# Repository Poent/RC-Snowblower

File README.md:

# RC Snowblower Project

====
LATEST UPDATES (10-26-2025):

Working on designing the impeller and auger portion of the snowblower. Switched from using a worm gear assembly to a custom ring and pinion setup using a spiral bevel gear. Motor is a 190KV motor being driven at 38v nominal. Motor at full power (which we'll never do) will spin at about 7,200 RPM. the motor goes through a 3:1 reduction to the impeller. Impeller will spin at <2400 RPM. The impeller drives the input shaft of the auger gearbox, which has a 9:1 reduction. At full power that will result in the auger at about 250rpm. All of these are design maximums. The motor will likely be RPM limited to 60% total power in the VESC, more than halving all these totals. 

Hello everyone! Welcome to my crazy project.

Before diving into the details, here’s quick background on me and why I’m building this. Feel free to skip down to the status if you want the meat.

=====

### Who I am
I’m a tech leader in the OT/MSP space with ~15 years in IT services. I own our MSP tool stack, cybersecurity program, and AI/automation initiatives. I’m CISSP-certified and studied electrical engineering, game development/design, and aviation management in college. I have a wonderful wife and two kids, and my hobbies include art, design, programming, 3D printing, woodworking, and more.

### How this project started
About two years ago my wife sent me a video of the Yarbo snowblower. It’s a tracked outdoor platform with attachments for mowing, snowblowing, hauling, etc., and it can go fully autonomous with an RTK/GNSS setup. I loved it… until I saw it was about $5,000, which I can’t justify for a <15-foot driveway.

Then she sent a smiliar (but different) 3D-printed snowblower video. Once again I was hyped to look at building it, but the "basic" kit alone was about $4,000. My dreams were dashed again—but the seed was planted.... I’ve got experience with CAD, 3D printing, and electronics, so I decided to try building my own!

That’s this project. While my BOM is under $4k... it is far more expensive than I initially anticipated and I have a far higher respect for those alternatives. 

### What to expect here
I can't honestly recommend anyone replicate this build. Better platforms exist, and I'm not an engineer! While I intend to make everything functional, resilient, and high quality... there WILL be problems. If you choose to follow along or, god forbid, try to build one of these yourself.... PLEASE understand what you're getting into. It WILL be a significant investment and there is NO garuntee of a working platform at the end of it. Please don't anticipate assistance of any kind if you choose to build this. BUT.... if you do... please tell me! I would love to see what other people do. I intend to make and keep this project fully open source, and I have no dreams of making this into a commercial product at any point in time. 

For those of you that want to just check it out and/or follow along - then sit back, and enjoy the ride!

## Status

**Completed**
- Chassis assembled with CNC aluminum frame and 3D-printed interconnects
- Power system using Headway 40152 LiFePO₄ cells and JK BMS
- V1 controller board designed, produced, soldered, and tested
- Basic ESP32 firmware with CRSF input and VESC CAN telemetry
- Initial drivetrain movement tests

**In Progress**
- Finalizing V1 firmware for the ESP32 and carrier board
- Universal mount for the snowblower attachment
- Track stress testing and refinement
- Chassis cover design and integration (sealed against snow)

**Planned**
- Blower attachment design and integration
- Public-ready docs for CAD, electronics, and firmware
- BOM refinement for cost and reliability

# LATEST IMAGES

# Progress

**Completed:**
- Chassis structure assembled with CNC aluminum frame and 3D-printed interconnects  
- Power system finalized around Headway LiFePO₄ cells and JK BMS (150A).
- Custom V1 of controller board - Designed, produced, soldered, and tested.
- Basic firmware running on ESP32 with input decoding and VESC telemetry working. 
- Initial testing of drivetrain and basic movement functions

**In Progress:**
- Finalize V1 Firmware for ESP32 and carrier board
- Design and implement universal mount for snowblower attachment. 
- Track stress testing and refinement
- Chassis cover design and integration (sealed against snow ingress) - NOT STARTED

**Future work:**
- Design blower attachment and integration.
- Preparing the project for public release (this repository) and planning documentation for CAD, electronics, and firmware.
- Refine parts list and BOM to reduce cost, complexity, and improve reliability.

## Overview
This repository will contain (wish list) the complete design and implementation files for a remote-controlled snowblower, including:

- **CAD Models**: 3D designs and mechanical components
- **Electronics**: Circuit designs, PCB layouts, and component specifications
- **Code**: Control software and firmware
- **Documentation**: Build guides, specifications, and user manuals
- **Images**: Photos, diagrams, and visual documentation
- **Build Log**: Chronological record of design iterations, testing, and modifications

## Repository Structure

```
├── CAD/           # 3D models, drawings, and mechanical designs
├── Code/          # Control software and firmware
├── Docs/          # Documentation and guides
├── Electronics/   # Circuit designs and electrical components
├── Images/        # Photos, diagrams, and visual documentation
└── Build_Log/    # Chronological record of design iterations and testing

```

## Features (Planned)
- [done] Remote control operation
- [done] Variable speed control
- [done] High-performance BLDC motors with custom gearboxes
- [ ] Weather-resistant design
- [ ] Modular component system
- [ ] Universal Mount for attachments (snowblower, plow, etc.)

### Wish List
- Autonomous navigation capabilities
- Real-time telemetry
- Produce fully open-source hardware and software
- Develop 3D printed versions of key components to reduce cost

## Hardware Requirements
*To be documented*

## Software Requirements
*To be documented*

## Getting Started
*Build instructions coming soon*

## Contributing
*Contribution guidelines to be added*

## License
*License information to be added*

## Contact
*Contact information to be added*

---
*This README will be updated as the project progresses.*

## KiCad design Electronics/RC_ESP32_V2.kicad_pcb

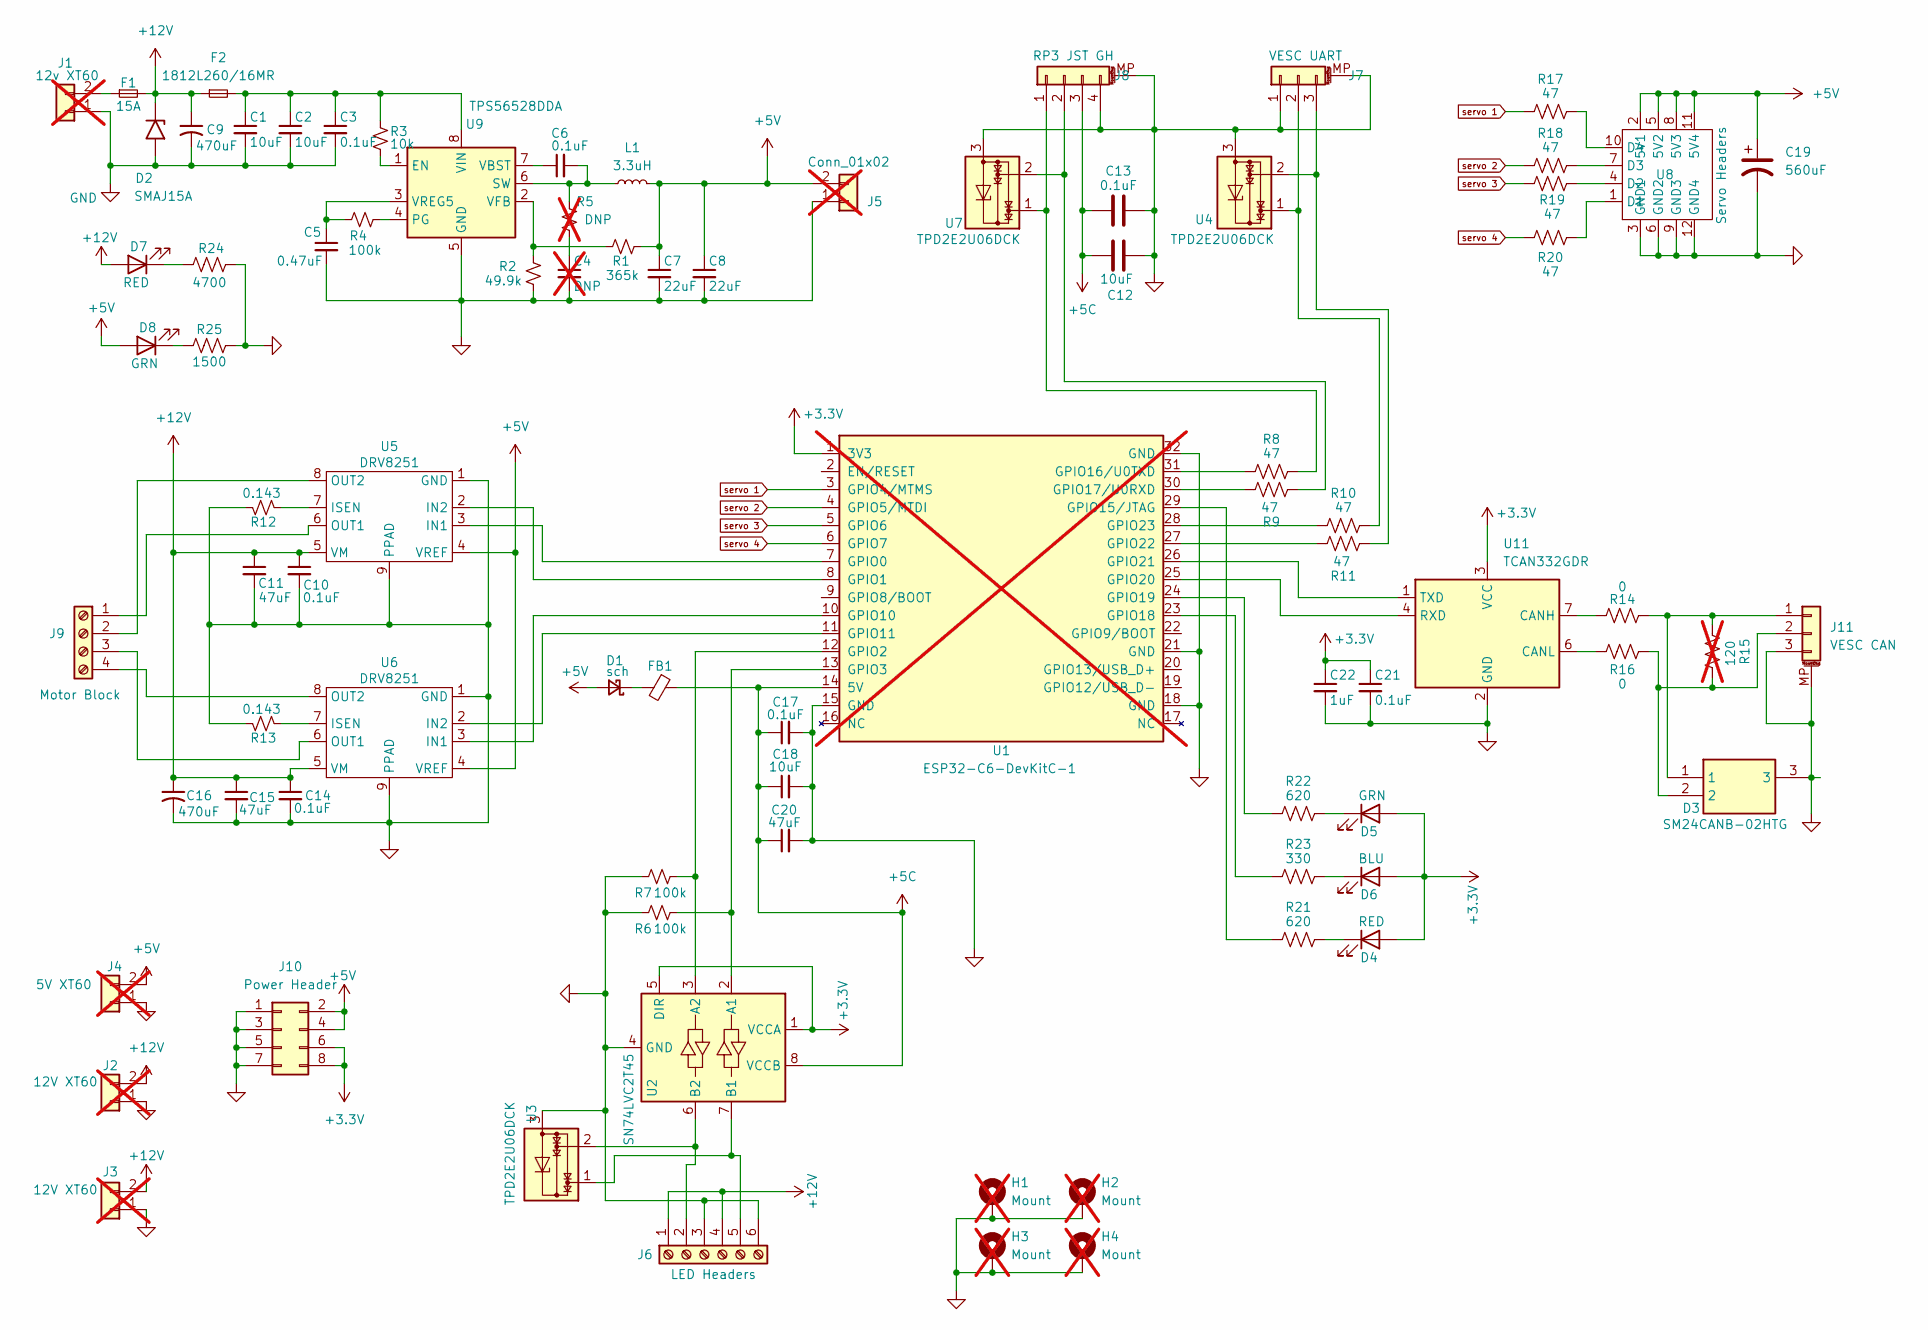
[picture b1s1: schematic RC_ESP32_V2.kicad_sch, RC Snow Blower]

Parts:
C1, C2, C12, C18: 10uF; C_0805_2012Metric_Pad1.18x1.45mm_HandSolder; MFG Part # GRM21BZ71E106KE15L
C3, C6, C10, C13, C14, C17, C21: 0.1uF; C_0805_2012Metric_Pad1.18x1.45mm_HandSolder; MFG Part # KGM21NR71E104KT
C4: DNP; C_0805_2012Metric_Pad1.18x1.45mm_HandSolder; not fitted
C5: 0.47uF; C_0805_2012Metric_Pad1.18x1.45mm_HandSolder; MFG Part # GRM188R71E474KA12D
C7, C8: 22uF; C_0805_2012Metric_Pad1.18x1.45mm_HandSolder; MFG Part # GRM21BR61C226ME44L
C9, C16: 470uF; CAP_EEHZU1E471P; MFG Part # EEH-ZU1E471P
C11, C15, C20: 47uF; C_1210_3225Metric_Pad1.33x2.70mm_HandSolder; MFG Part # TMK325ABJ476MM-P
C19: 560uF; CP_Elec_10x7.9; MFG Part # 10SVP560M
C22: 1uF; C_0805_2012Metric_Pad1.18x1.45mm_HandSolder; MFG Part # GRM21BR71A105KA01K
D1: sch; D_SOD-123; MFG Part # B5819W
D2: SMAJ15A; D_SMA; MFG Part # SMAJ15A
D3: SM24CANB-02HTG; SM24CANB02HTG; Manufacturer_Part_Number SM24CANB-02HTG; Mouser Part Number 576-SM24CANB-02HTG
D4, D7: RED; LED_1206_3216Metric_Pad1.42x1.75mm_HandSolder; MFG Part # QTLP650D2TR
D5, D8: GRN; LED_1206_3216Metric_Pad1.42x1.75mm_HandSolder; MFG Part # QTLP650D4TR/QT15-21SYGD/S530-E2/TR8
D6: BLU; LED_1206_3216Metric_Pad1.42x1.75mm_HandSolder; MFG Part # HSMR-C150
F1: 15A; Fuseholder_Blade_Mini_Keystone_3568; MFG Part # 36-3568-ND
F2: 1812L260/16MR; Fuse_1812_4532Metric_Pad1.30x3.40mm_HandSolder; MFG Part # 1812L260/16MR
FB1: FerriteBead_Small; 0805; MFG Part # BLM21PG121SN1D
H1, H2, H3, H4: Mount; MountingHole_4.3mm_M4_Pad_Via; not fitted
J1: 12v XT60; AMASS_XT60-M_1x02_P7.20mm_Vertical; MFG Part # XT60-M; not fitted
J2, J3: 12V XT60; AMASS_XT60-F_1x02_P7.20mm_Vertical; MFG Part # XT60-F; not fitted
J4: 5V XT60; AMASS_XT60-F_1x02_P7.20mm_Vertical; MFG Part # XT60-F; not fitted
J5: Conn_01x02; AMASS_XT60-F_1x02_P7.20mm_Vertical; MFG Part # XT60-F; not fitted
J6: LED Headers; TerminalBlock_TE_282834-6_1x06_P2.54mm_Horizontal; MFG Part # OSTVN06A150
J7: VESC UART; JST_GH_BM03B-GHS-TBT_1x03-1MP_P1.25mm_Vertical; MFG Part # BM03B-GHS-TBT
J8: RP3 JST GH; JST_GH_BM04B-GHS-TBT_1x04-1MP_P1.25mm_Vertical; MFG Part # SM04B-GHS-TB
J9: Motor Block; TerminalBlock_TE_282834-4_1x04_P2.54mm_Horizontal; MFG Part # OSTVN04A150
J10: Power Header; PinSocket_2x04_P2.54mm_Vertical; MFG Part # PPTC042LFBN-RC
J11: VESC CAN; JST_GH_BM03B-GHS-TBT_1x03-1MP_P1.25mm_Vertical; MFG Part # BM03B-GHS-TBT
L1: 3.3uH; L_Wurth_WE-HCC-8070; MFG Part # 7443340330
R1: 365k; R_0805_2012Metric_Pad1.20x1.40mm_HandSolder; MFG Part # ERA-6AEB3653V
R2: 49.9k; R_0805_2012Metric_Pad1.20x1.40mm_HandSolder; MFG Part # ERA-6AEB4992V
R3: 10k; R_0805_2012Metric_Pad1.20x1.40mm_HandSolder; MFG Part # ERA-6AEB103V
R4, R6, R7: 100k; R_0805_2012Metric_Pad1.20x1.40mm_HandSolder; MFG Part # ERA-6AEB104V
R5: DNP; R_0805_2012Metric_Pad1.20x1.40mm_HandSolder; not fitted
R8, R9, R10, R11, R17, R18, R19, R20: 47; R_0805_2012Metric_Pad1.20x1.40mm_HandSolder; MFG Part # CRGCQ0805F47R
R12, R13: 0.143; R_2512_6332Metric_Pad1.40x3.35mm_HandSolder; MFG Part # RLC73PW3AR143FTDG
R14, R16: 0; R_0805_2012Metric_Pad1.20x1.40mm_HandSolder; MFG Part # CR0805-J/-000ELF
R15: 120; R_0805_2012Metric_Pad1.20x1.40mm_HandSolder; MFG Part # ERA-6AEB101V; not fitted
R21, R22: 620; R_0805_2012Metric_Pad1.20x1.40mm_HandSolder; MFG Part # RC0805FR-07620RL
R23: 330; R_0805_2012Metric_Pad1.20x1.40mm_HandSolder; MFG Part # AC0805FR-07330RL
R24: 4700; R_0805_2012Metric_Pad1.20x1.40mm_HandSolder; MFG Part # AC0805FR-074K7L
R25: 1500; R_0805_2012Metric_Pad1.20x1.40mm_HandSolder; MFG Part # RC0805JR-071K5L
U1: ESP32-C6-DevKitC-1; not fitted
U2: SN74LVC2T45; SSOP-8_2.95x2.8mm_P0.65mm; MFG Part # SN74LVC2T45DCUR
U3, U4, U7: TPD2E2U06DCK; SOT-323_SC-70; MFG Part # TPD2E2U06DCKR
U5, U6: DRV8251; TI_SO-PowerPAD-8; MFG Part # DRV8251DDAR
U8: Servo Headers; 03x04 Generic Pin Header; MFG Part # TSW-104-07-L-T
U9: TPS56528DDA; Texas_HSOP-8-1EP_3.9x4.9mm_P1.27mm_ThermalVias; MFG Part # TPS56528DDAR
U11: TCAN332GDR; SOIC-8_3.9x4.9mm_P1.27mm; MFG Part # TCAN332GDR

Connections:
+3.3V: C21.1, C22.1, D4.2 (A), D5.2 (A), D6.2 (A), J10.6, J10.8, U1.1 (3V3), U2.1 (VCCA), U2.5 (DIR), U11.3 (VCC)
+5C: C12.1, C13.1, C17.1, C18.1, C20.1, FB1.1, J8.3, U1.14 (5V), U2.8 (VCCB)
+5V: C7.1, C8.1, C19.1, D1.2 (A), D8.2 (A), J4.2, J5.2, J10.2, J10.4, L1.2, R1.1, U5.4 (VREF), U6.4 (VREF), U8.2 (5V1), U8.5 (5V2), U8.8 (5V3), U8.11 (5V4)
+12V: C9.1, C10.1, C11.1, C14.1, C15.1, C16.1, D2.1 (A1), D7.2 (A), F1.2, F2.1, J2.2, J3.2, J6.1, J6.4, U5.5 (VM), U6.5 (VM)
GND: C1.2, C2.2, C3.2, C4.2, C5.2, C7.2, C8.2, C9.2, C10.2, C11.2, C12.2, C13.2, C14.2, C15.2, C16.2, C17.2, C18.2, C19.2, C20.2, C21.2, C22.2, D2.2 (A2), D3.3, H1.1, H2.1, H3.1, H4.1, J1.1, J2.1, J3.1, J4.1, J5.1, J6.3, J6.6, J7.1, J7.MP (MountPin), J8.4, J8.MP (MountPin), J10.1, J10.3, J10.5, J10.7, J11.3, J11.MP (MountPin), R2.1, R6.1, R7.1, R12.2, R13.2, R24.1, R25.2, U1.15 (GND), U1.18 (GND), U1.21 (GND), U1.32 (GND), U2.4 (GND), U3.3, U4.3, U5.1 (GND), U5.9 (PPAD), U6.1 (GND), U6.9 (PPAD), U7.3, U8.3 (GND1), U8.6 (GND2), U8.9 (GND3), U8.12 (GND4), U9.5 (GND), U9.9 (GND), U11.2 (GND)
unnamed: C4.1, R5.2
unnamed: D1.1 (K), FB1.2
unnamed: D4.1 (K), R21.2
unnamed: D5.1 (K), R22.2
unnamed: D6.1 (K), R23.2
unnamed: D7.1 (K), R24.2
unnamed: D8.1 (K), R25.1
unnamed: F1.1, J1.2
unnamed: J6.2, U2.6 (B2), U3.2
unnamed: J6.5, U2.7 (B1), U3.1
unnamed: J7.2, R10.2, U4.1
unnamed: J7.3, R11.2, U4.2
unnamed: J8.1, R8.2, U7.1
unnamed: J8.2, R9.2, U7.2
unnamed: J9.1, U5.6 (OUT1)
unnamed: J9.2, U5.8 (OUT2)
unnamed: J9.3, U6.6 (OUT1)
unnamed: J9.4, U6.8 (OUT2)
unnamed: D3.1, J11.1, R14.1, R15.2
unnamed: D3.2, J11.2, R15.1, R16.1
unnamed: U1.7 (GPIO0), U5.3 (IN1)
unnamed: U1.8 (GPIO1), U5.2 (IN2)
unnamed: R7.2, U1.12 (GPIO2), U2.3 (A2)
unnamed: R6.2, U1.13 (GPIO3), U2.2 (A1)
unnamed: U1.10 (GPIO10), U6.3 (IN1)
unnamed: U1.11 (GPIO11), U6.2 (IN2)
unnamed: R21.1, U1.29 (GPIO15/JTAG)
unnamed: R8.1, U1.31 (GPIO16/U0TXD)
unnamed: R9.1, U1.30 (GPIO17/U0RXD)
unnamed: R23.1, U1.23 (GPIO18)
unnamed: R22.1, U1.24 (GPIO19)
unnamed: U1.25 (GPIO20), U11.4 (RXD)
unnamed: U1.26 (GPIO21), U11.1 (TXD)
unnamed: R11.1, U1.27 (GPIO22)
unnamed: R10.1, U1.28 (GPIO23)
unnamed: R12.1, U5.7 (ISEN)
unnamed: R13.1, U6.7 (ISEN)
unnamed: R20.2, U8.1 (D1)
unnamed: R19.2, U8.4 (D2)
unnamed: R18.2, U8.7 (D3)
unnamed: R17.2, U8.10 (D4)
unnamed: R3.2, U9.1 (EN)
unnamed: R4.1, U9.4 (PG)
unnamed: C6.2, L1.1, R5.1, U9.6 (SW)
unnamed: C6.1, U9.7 (VBST)
unnamed: R1.2, R2.2, U9.2 (VFB)
unnamed: C1.1, C2.1, C3.1, F2.2, R3.1, U9.8 (VIN)
unnamed: C5.1, R4.2, U9.3 (VREG5)
unnamed: R14.2, U11.7 (CANH)
unnamed: R16.2, U11.6 (CANL)
servo 1: R17.1, U1.3 (GPIO4/MTMS)
servo 2: R18.1, U1.4 (GPIO5/MTDI)
servo 3: R19.1, U1.5 (GPIO6)
servo 4: R20.1, U1.6 (GPIO7)

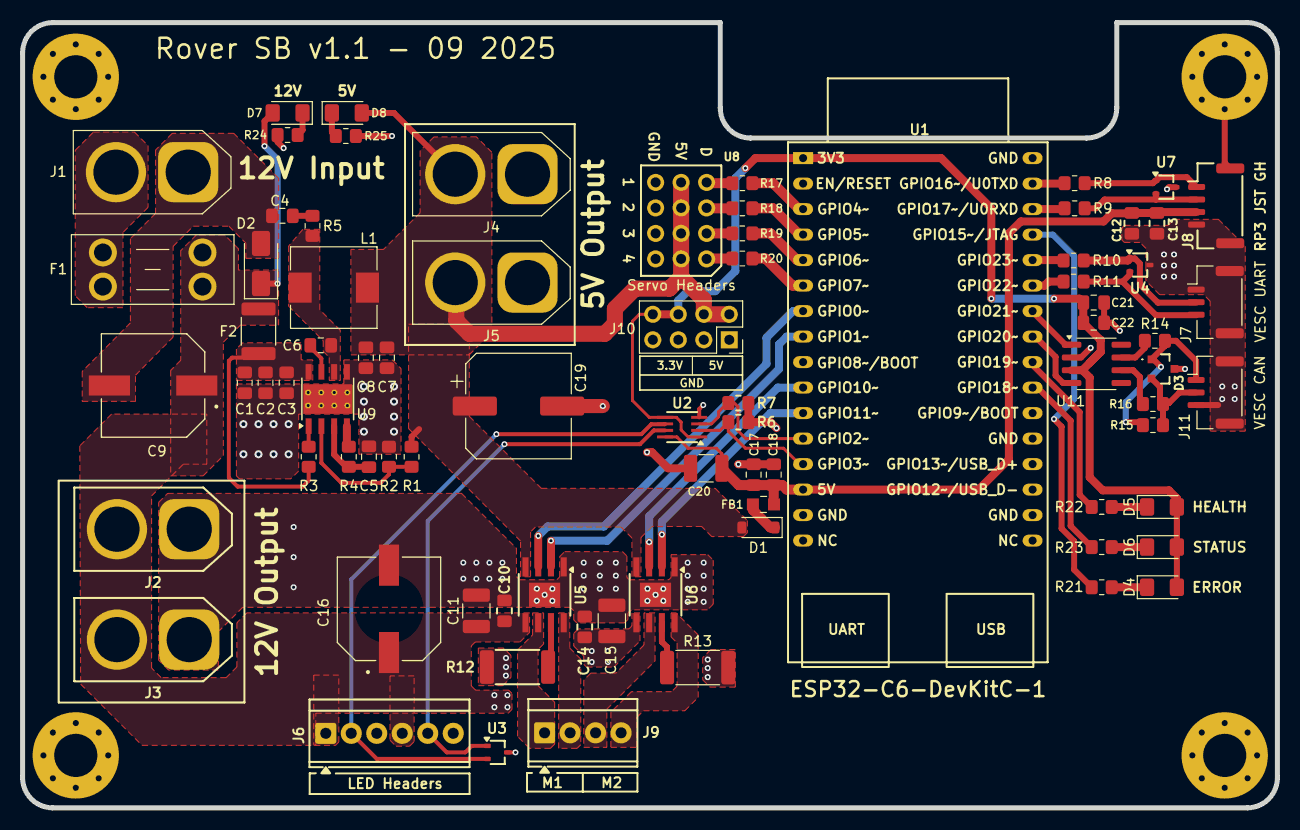
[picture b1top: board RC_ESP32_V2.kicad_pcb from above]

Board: 2 copper layers, 125.0 x 78.2 mm, 84 parts (0 on the bottom side), 59 nets.

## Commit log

2025-09-28 Initial commit: Add README.md with project overview, status, features, and structure
2025-09-28 Add latest images to README
    Added latest images showcasing project progress and updates.
2025-09-28 Clean up README by removing unused image URL
    Removed an unnecessary image URL from the README.
2025-09-28 Update README with additional images
    Added new images to the README for better visualization.
2025-09-28 uploaded progress images.
2025-09-28 Build Repo structure
2025-09-28 Add progress section to README
2025-10-01 Minor updates to Readme. Reworking AI generated details from first draft.
    Expanded project description and status updates, including personal background and project expectations.
